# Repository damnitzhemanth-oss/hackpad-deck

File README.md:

# MacroPad
A 9-key *multi-functional* macropad with rotary encoder, OLED, and addressable RGB LEDs

*Note : This ReadMe is written by a human known as Hemanth from India, I am new to this and learning every day. Please highlight the mistakes I may have made.*

## Overview

This is my first **Stardance HackClub** project. I have officially worked on this project for 22+ hours. I want to thank all the people to who are responsible in creation of these organizations. 

## Functions 

- Modes like Dev, Editor, etc with different presets of keys.
- Contains a satisfying Mini Game.
(*Discussed in **depth** in upcoming sections*)

## PCB  Design

I was already well versed with simple hardware projects using **Arduino UNO** and **ESP 8266**, but even though I knew about PCBs I never used them as they are expensive. Learning *KiCad* was pretty straight forward and easy.

Mainly routing was a bit challenging but everything else was easy. DRC have 0 errors except silkscreen warnings. 

## PCB Gallery

1. SCHEMATIC SVG 

2. Screenshots

## CAD Design

Cad was one of the field I had zero ball knowledge about. So designing it was fun but also was a pain. Due to daily internet cap I was not able to download Fusion 360, so OnShape was the way to go.
The design mainly consists of Base plate with Heatset Inserts and Top Plate with holes for M3 screws. PCB gets sandwiched between. All this was done in keeping +0.2 mm tolerance in mind.

## Cad Gallery.

##  Functions

| Feature | Description |
|---------|-------------|
|  **6 Modes** | Dev, Media, Video, Macro, Aesthetic, Games |
|  **Whack-a-LED Game** | Press the lit switch before time runs out |
| **DJ Mode** | Rainbow RGB animation across all 9 LEDs |
|  **Snowfall OLED** | Idle screen shows falling snowflakes |
|  **Rotary Encoder** | Volume control on every mode |
| **Per-Key RGB** | 9 addressable SK6812MINI-E LEDs |
|  **Live OLED Feedback** | Shows mode, key presses, and game score |

---

##  Modes

Cycle modes by **long-pressing SW7** (bottom-left key).

### 1. DEV — Editor & Typing
| Key | Action |
|-----|--------|
| SW1–SW9 | Number keys 2–9 (numpad layout) |
| SW7 (tap) | ESC |
| SW7 (hold) | Next mode |

### 2. MEDIA — Playback Controls
| Key | Action |
|-----|--------|
| SW1 | Play / Pause |
| SW2 | Stop |
| SW3 | Mute |
| SW4 | Previous Track |
| SW6 | Next Track |
| SW8 | Volume Down |
| SW9 | Volume Up |

### 3. VIDEO — DaVinci Resolve Editing
| Key | Action |
|-----|--------|
| SW1 | Split Clip |
| SW2 | Undo |
| SW3 | Redo |
| SW4 | Mark In |
| SW5 | Mark Out |
| SW6 | Paste Attributes |
| SW8 | Play / Pause |
| SW9 | Backspace |

### 4. MACRO — Launcher & Productivity
| Key | Action |
|-----|--------|
| SW1–SW3 | Open App 1 / 2 / 3 |
| SW4–SW6 | Copy / Paste / Cut |
| SW8–SW9 | Select All / Save |

### 5. AESTHETIC — DJ Mode 
RGB LEDs dance through a rotating rainbow. No key output — pure visual vibes.

### 6. GAMES — Whack-a-LED 
A random LED lights up **green**. Press its switch within **3 seconds** to score. Wrong key or timeout resets your score to 0 and flashes all LEDs red.

---

## Bill of Materials

| # | Component | Qty | Source |
|---|-----------|-----|--------|
| 1 | Seeed XIAO RP2040 | 1 | Hack Club Kit |
| 2 | Gateron KS-3 MX Switches | 9 | Hack Club Kit |
| 3 | 1N4148 Through-hole Diodes | 9 | Hack Club Kit |
| 4 | Alps EC11E Rotary Encoder | 1 | Hack Club Kit |
| 5 | SK6812MINI-E RGB LEDs | 9 | Hack Club Kit |
| 6 | 0.91" SSD1306 OLED Display (128×32) | 1 | Hack Club Kit |
| 7 | White DSA Keycaps | 9 | Hack Club Kit |
| 8 | M3×16mm Screws *(trim to 13mm)* | 4 | Hack Club Kit |
| 9 | M3×5mm×4mm Heatset Inserts | 4 | Hack Club Kit |
| 10 | 3D Printed Case (Base + Top Plate) | 1 set | 

---

## Firmware

Written in **Python** using **KMK** on **CircuitPython**.

See [`Firmware/main.py`](Firmware/main.py) for the full source.

---

## AI USAGE

I used AI/ Online resources to learn but never automate anything. You can checkout Lapse recording from lookout too.

## Credits

- **[Hack Club](https://hackclub.com/)** — for the kit and the program
- **Star Dance** — for organizing this buildathon
- **[KMK Firmware](https://github.com/KMKfw/kmk_firmware)** — Python keyboard firmware
- **Hack Club Hackpad team** — for the guides and KiCad care package
- Special shoutout to Logan Peterson, whose design inspired me a lot.

---

##  License

Open source, but you are responsible if it creates a black hole in your house.

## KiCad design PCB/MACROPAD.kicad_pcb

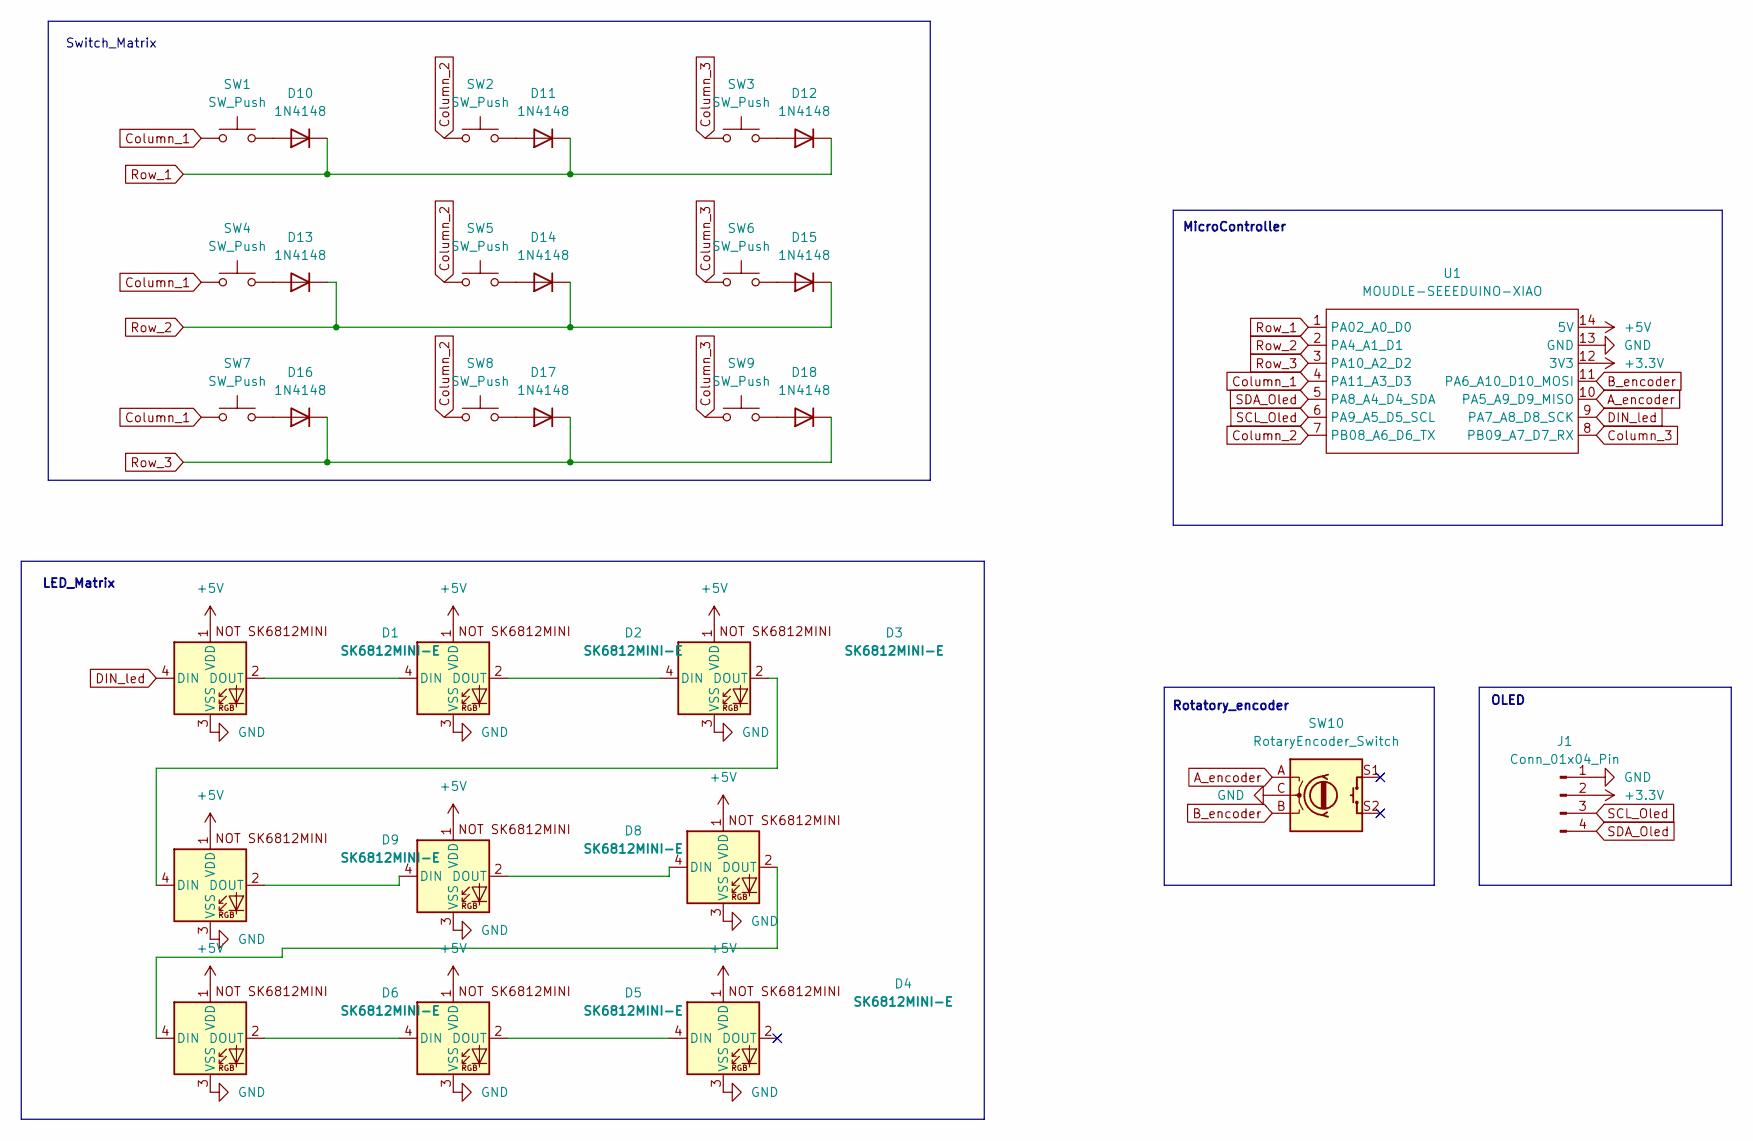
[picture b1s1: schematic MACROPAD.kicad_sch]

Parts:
D1, D2, D3, D4, D5, D6, D7, D8, D9: SK6812MINI-E; MX_SK6812MINI-E_fixed_mount_with3D
D10, D11, D12, D13, D14, D15, D16, D17, D18: 1N4148; D_DO-35_SOD27_P7.62mm_Horizontal
J1: Conn_01x04_Pin; Adafruit_SSD1306
SW1, SW2, SW3, SW4, SW5, SW6, SW7, SW8, SW9: SW_Push; SW_Cherry_MX_1.00u_PCB_3d
SW10: RotaryEncoder_Switch; RotaryEncoder_Alps_EC11E-Switch_Vertical_H20mm
U1: MOUDLE-SEEEDUINO-XIAO; XIAO-Generic-Hybrid-14P-2.54-21X17.8MM

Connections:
+3.3V: J1.2, U1.12 (3V3)
+5V: D1.1 (VDD), D2.1 (VDD), D3.1 (VDD), D4.1 (VDD), D5.1 (VDD), D6.1 (VDD), D7.1 (VDD), D8.1 (VDD), D9.1 (VDD), U1.14 (5V)
A_encoder: SW10.A, U1.10 (PA5_A9_D9_MISO)
B_encoder: SW10.B, U1.11 (PA6_A10_D10_MOSI)
Column_1: SW1.1, SW4.1, SW7.1, U1.4 (PA11_A3_D3)
Column_2: SW2.1, SW5.1, SW8.1, U1.7 (PB08_A6_D6_TX)
Column_3: SW3.1, SW6.1, SW9.1, U1.8 (PB09_A7_D7_RX)
DIN_led: D1.4 (DIN), U1.9 (PA7_A8_D8_SCK)
GND: D1.3 (VSS), D2.3 (VSS), D3.3 (VSS), D4.3 (VSS), D5.3 (VSS), D6.3 (VSS), D7.3 (VSS), D8.3 (VSS), D9.3 (VSS), J1.1, SW10.C, U1.13 (GND)
unnamed: D1.2 (DOUT), D2.4 (DIN)
unnamed: D2.2 (DOUT), D3.4 (DIN)
unnamed: D3.2 (DOUT), D9.4 (DIN)
unnamed: D4.4 (DIN), D5.2 (DOUT)
unnamed: D5.4 (DIN), D6.2 (DOUT)
unnamed: D6.4 (DIN), D7.2 (DOUT)
unnamed: D7.4 (DIN), D8.2 (DOUT)
unnamed: D8.4 (DIN), D9.2 (DOUT)
unnamed: D10.2 (A), SW1.2
unnamed: D11.2 (A), SW2.2
unnamed: D12.2 (A), SW3.2
unnamed: D13.2 (A), SW4.2
unnamed: D14.2 (A), SW5.2
unnamed: D15.2 (A), SW6.2
unnamed: D16.2 (A), SW7.2
unnamed: D17.2 (A), SW8.2
unnamed: D18.2 (A), SW9.2
Row_1: D10.1 (K), D11.1 (K), D12.1 (K), U1.1 (PA02_A0_D0)
Row_2: D13.1 (K), D14.1 (K), D15.1 (K), U1.2 (PA4_A1_D1)
Row_3: D16.1 (K), D17.1 (K), D18.1 (K), U1.3 (PA10_A2_D2)
SCL_Oled: J1.3, U1.6 (PA9_A5_D5_SCL)
SDA_Oled: J1.4, U1.5 (PA8_A4_D4_SDA)

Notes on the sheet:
LED_Matrix
MicroController
Rotatory_encoder
Switch_Matrix
OLED

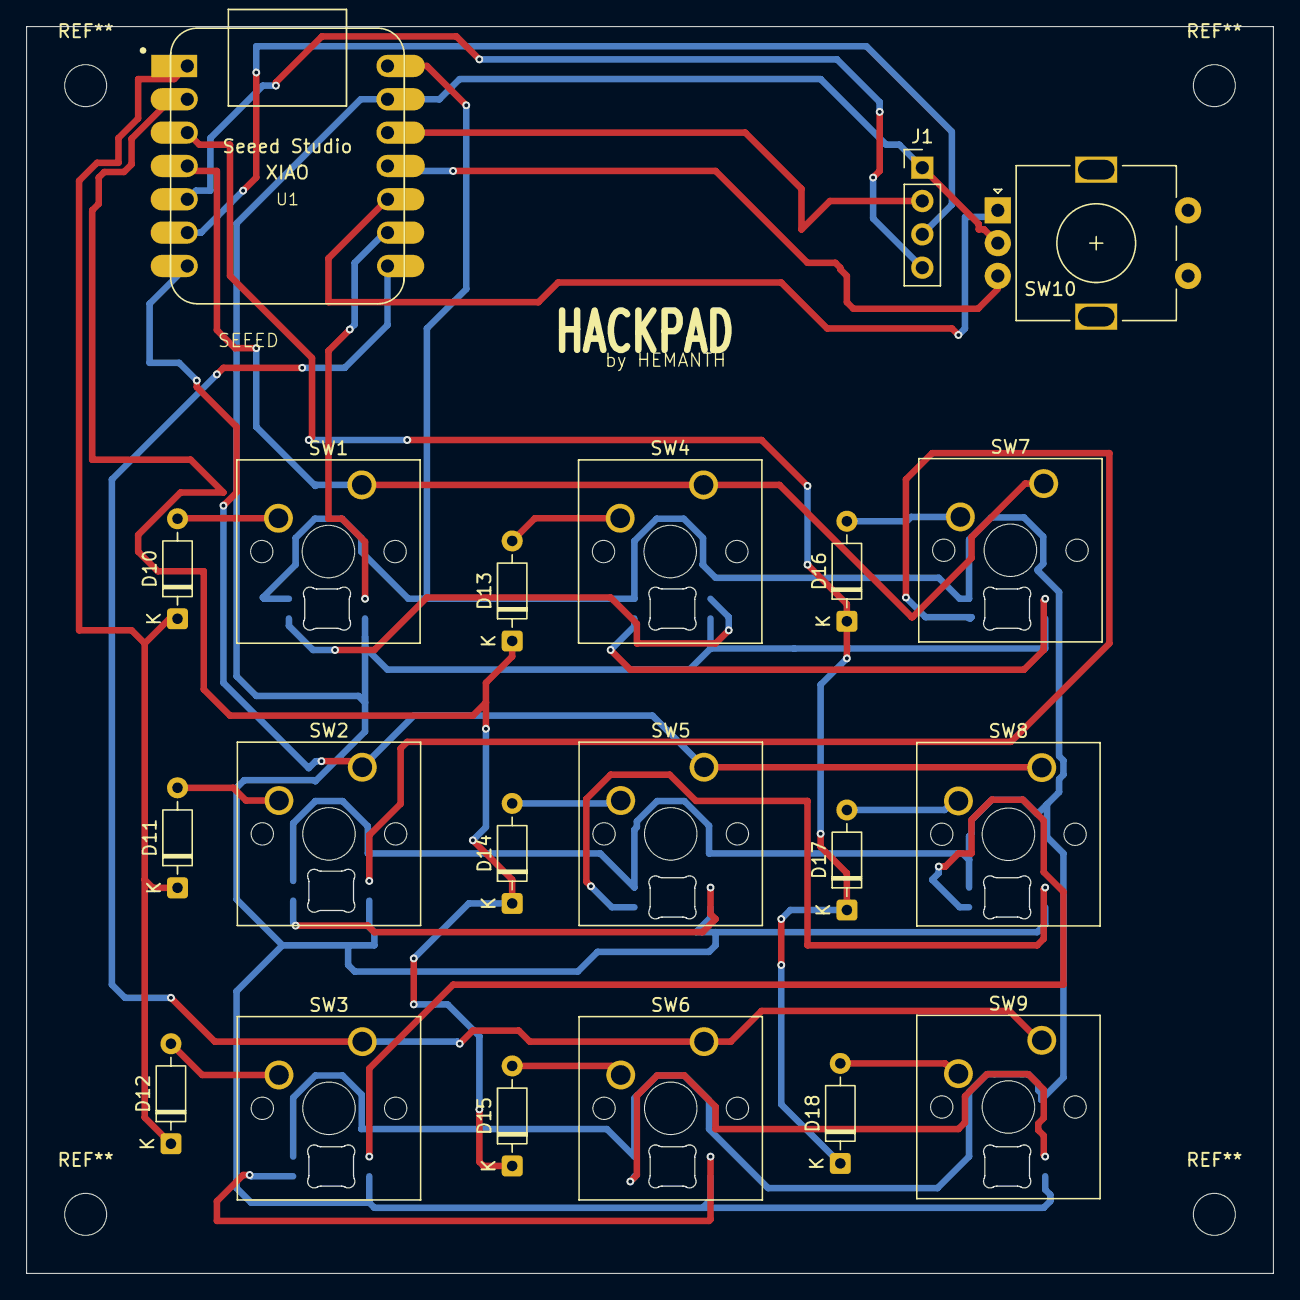
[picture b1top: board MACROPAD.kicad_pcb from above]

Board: 2 copper layers, 95.0 x 95.0 mm, 30 parts (0 on the bottom side), 31 nets.
